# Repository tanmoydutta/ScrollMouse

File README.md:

# Scroll Mouse using manetic angle sensor
A BLE mouse dial for smooth and minimum effort scrolling. 

Powered by nRF52840 BLE Soc, this HID input device is to reduce effort in scrolling. 

## Demo

_Click the image to watch the video._

Here is an open view of the device - 

Here is a complete 3D view of the device - 

The PCB is designed around AS5600 mangetic engle encoder- 

In the center is a 608 2RS Bearing for long boards making the swivel action smooth and long running -

The radial magnet in the center of the bearing floats on top of the AS5600 sensor chip to detect the angle of rotation -

The diametrically magnetised permanent magnet sits in the center of the dial assembly - 

This project is certified as Open Source Hardware - 
<p align="center">
  
</p>

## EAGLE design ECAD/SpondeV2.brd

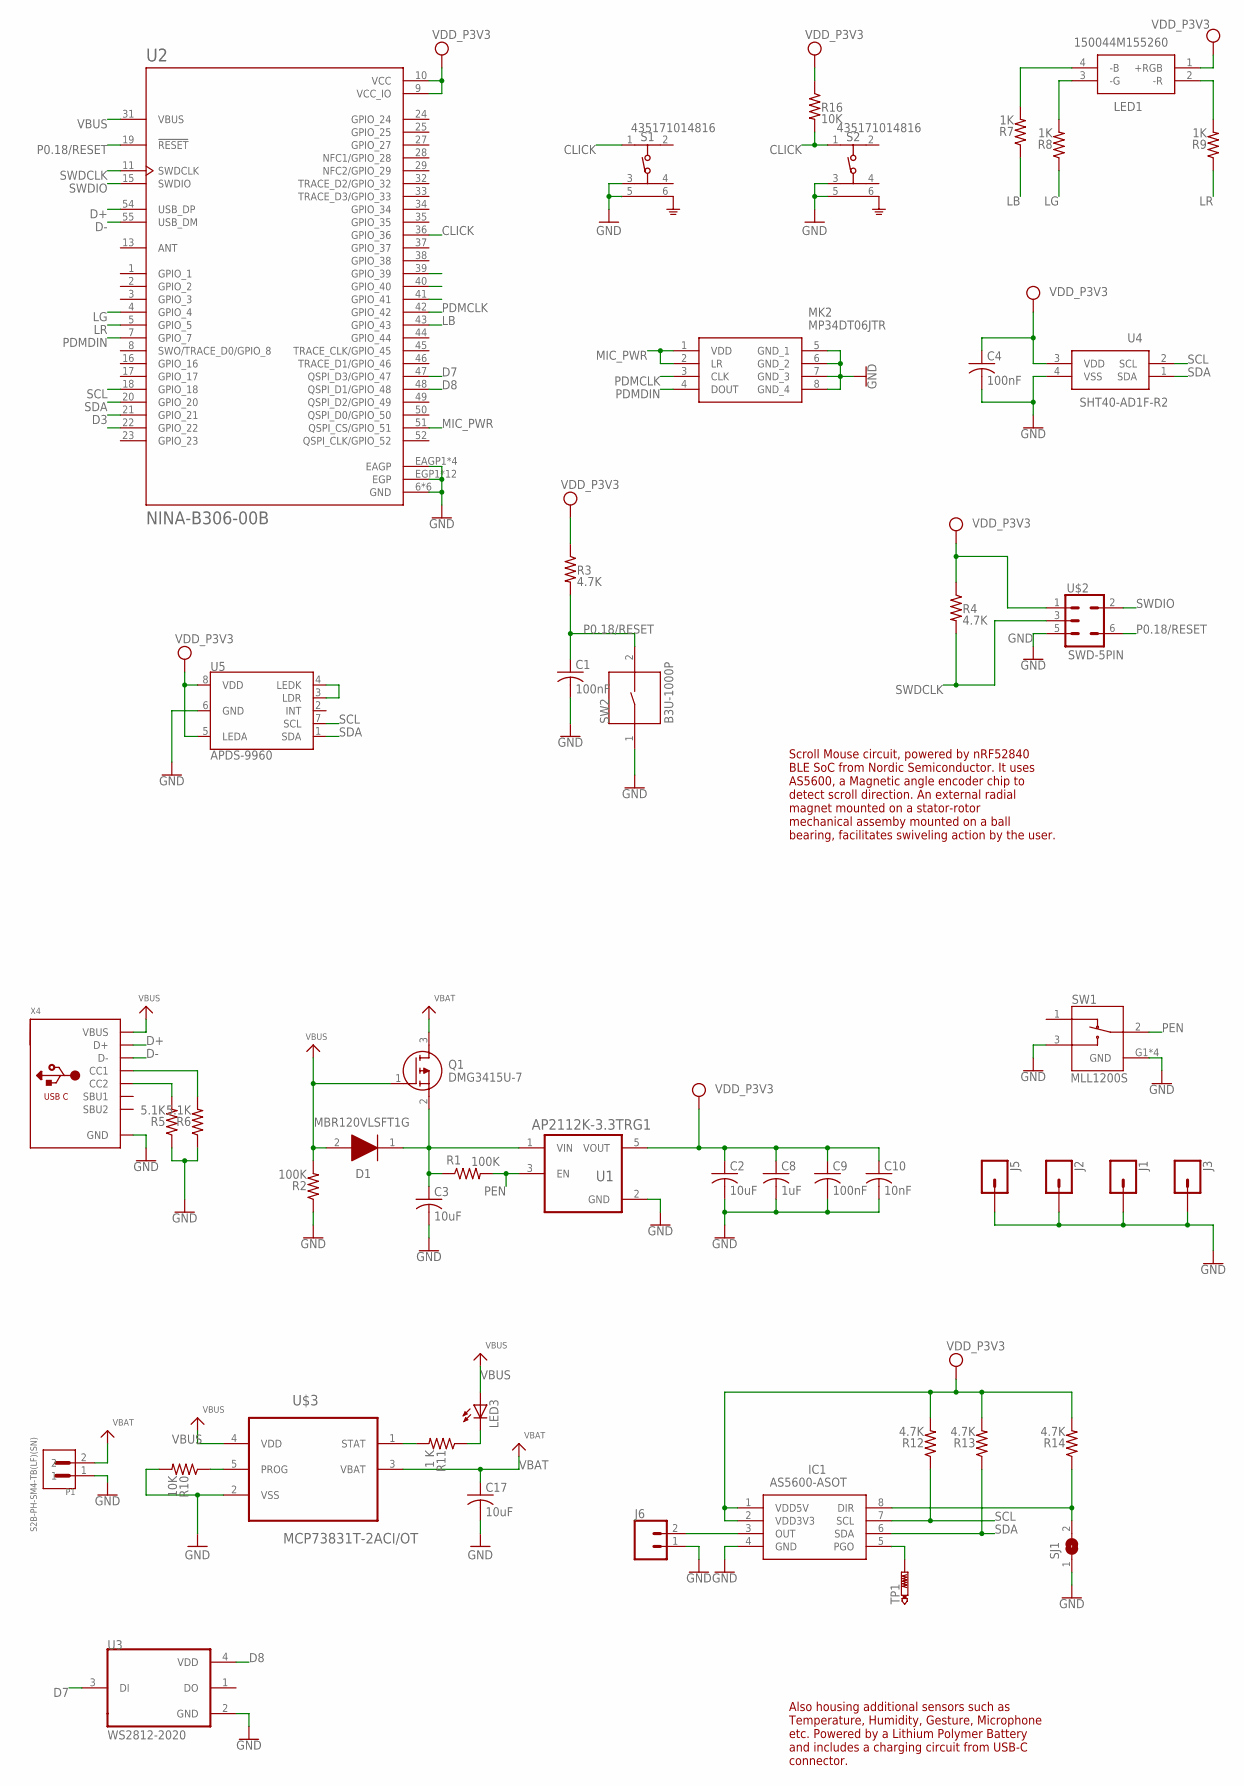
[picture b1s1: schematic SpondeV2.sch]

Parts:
C1, C4, C9: 100nF; C0402
C2, C3, C17: 10uF; C0402
C8: 1uF; C0402
C10: 10nF; C0402
D1: MBR120VLSFT1G; SODFL3616X98N
IC1: AS5600-ASOT; SOIC127P600X175-8N
J1, J2, J3, J5: CONN_01PTH_2MM; 1X01_2MM
J6: CONN_02LOCK_LONGPADS; 1X02_LOCK_LONGPADS
LED1: 150044M155260
LED3: LEDCHIPLED_0603; CHIPLED_0603
MK2: MP34DT06JTR
P1: S2B-PH-SM4-TB(LF)(SN); JST_S2B-PH-SM4-TB(LF)(SN)
Q1: DMG3415U-7; SOT96P240X100-3N
R1, R2: 100K; R0402
R3, R4, R12, R13, R14: 4.7K; R0402
R5, R6: 5.1K; R0402
R7, R8, R9: 1K; R0402
R10, R16: 10K; R0402
R11: 1 K; R0402
S1, S2: 435171014816
SJ1: SJ
SW1: MLL1200S; SW_MLL1200S
SW2: B3U-1000P; SW_B3U-1000P
TP1: PTR1B2,54; B2,54
U1: AP2112K-3.3TRG1; SOT95P285X140-5N
U2: NINA-B306-00B; XCVR_NINA-B306-00B
U3: WS2812-2020; LED_WS2812-2020
U4: SHT40-AD1F-R2; SHT40AD1FR2
U5: APDS-9960
U$2: SWD-5PIN; PAD_05_03X2_TP_NO4
U$3: MCP73831T-2ACI/OT; SOT95P280X145-5N
X4: MICROBUILDER_USB_C; MICROBUILDER_USB_C_CUSB31-CFM2AX-01-X

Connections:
CLICK: R16.2, S1.1, S2.1, U2.36 (GPIO_36)
D3: U2.21 (GPIO_21)
D7: U2.47 (QSPI_D3/GPIO_47), U3.3 (DI)
D8: U2.48 (QSPI_D1/GPIO_48), U3.4 (VDD)
D+: U2.54 (USB_DP), X4.A6 (D+), X4.B6 (D+)
D-: U2.55 (USB_DM), X4.A7 (D-), X4.B7 (D-)
GND: C1.2, C2.2, C3.2, C4.2, C8.2, C9.2, C10.2, C17.2, IC1.4 (GND), J1.1, J2.1, J3.1, J5.1, J6.1, MK2.5 (GND_1), MK2.6 (GND_2), MK2.7 (GND_3), MK2.8 (GND_4), P1.1, R2.1, R5.1, R6.1, R10.2, S1.3, S1.5, S2.3, S2.5, SJ1.1, SW1.3, SW1.G1 (GND), SW1.G2 (GND), SW1.G3 (GND), SW1.G4 (GND), SW2.1, U1.2 (GND), U2.6 (GND), U2.12 (GND), U2.14 (GND), U2.26 (GND), U2.30 (GND), U2.53 (GND), U2.EAGP1 (EAGP), U2.EAGP2 (EAGP), U2.EAGP3 (EAGP), U2.EAGP4 (EAGP), U2.EGP1 (EGP), U2.EGP2 (EGP), U2.EGP3 (EGP), U2.EGP4 (EGP), U2.EGP5 (EGP), U2.EGP6 (EGP), U2.EGP7 (EGP), U2.EGP8 (EGP), U2.EGP9 (EGP), U2.EGP10 (EGP), U2.EGP11 (EGP), U2.EGP12 (EGP), U3.2 (GND), U4.4 (VSS), U5.6 (GND), U$2.5, U$3.2 (VSS), X4.A1B12 (GND), X4.B1A12 (GND)
LB: R7.1, U2.43 (GPIO_43)
LG: R8.1, U2.4 (GPIO_4)
LR: R9.1, U2.5 (GPIO_5)
MIC_PWR: MK2.1 (VDD), MK2.2 (LR), U2.51 (QSPI_CS/GPIO_51)
unnamed: IC1.5 (PGO), TP1.TP
unnamed: R11.2, U$3.1 (STAT)
unnamed: R5.2, X4.B5 (CC2)
unnamed: R6.2, X4.A5 (CC1)
unnamed: C3.1, D1.1 (K), Q1.2 (S), R1.1, U1.1 (VIN)
unnamed: U5.3 (LDR), U5.4 (LEDK)
unnamed: IC1.8 (DIR), R14.1, SJ1.2
unnamed: IC1.3 (OUT), J6.2
unnamed: LED1.4 (-B), R7.2
unnamed: LED1.3 (-G), R8.2
unnamed: R10.1, U$3.5 (PROG)
unnamed: LED3.C, R11.1
unnamed: LED1.2 (-R), R9.2
P0.18/RESET: C1.1, R3.2, SW2.2, U2.19 (!RESET), U$2.6
PDMCLK: MK2.3 (CLK), U2.42 (GPIO_42)
PDMDIN: MK2.4 (DOUT), U2.7 (GPIO_7)
PEN: R1.2, SW1.2, U1.3 (EN)
SCL: IC1.7 (SCL), R12.1, U2.18 (GPIO_18), U4.2 (SCL), U5.7 (SCL)
SDA: IC1.6 (SDA), R13.1, U2.20 (GPIO_20), U4.1 (SDA), U5.1 (SDA)
SWDCLK: R4.2, U2.11 (SWDCLK), U$2.3
SWDIO: U2.15 (SWDIO), U$2.2
VBAT: C17.1, P1.2, Q1.3 (D), U$3.3 (VBAT)
VBUS: D1.2 (A), LED3.A, Q1.1 (G), R2.2, U2.31 (VBUS), U$3.4 (VDD), X4.A4B9 (VBUS), X4.B4A9 (VBUS)
VCC: C2.1, C4.1, C8.1, C9.1, C10.1, IC1.1 (VDD5V), IC1.2 (VDD3V3), LED1.1 (+RGB), R3.1, R4.1, R12.2, R13.2, R14.2, R16.1, U1.5 (VOUT), U2.9 (VCC_IO), U2.10 (VCC), U4.3 (VDD), U5.5 (LEDA), U5.8 (VDD), U$2.1

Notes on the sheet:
Scroll Mouse circuit, powered by nRF52840 BLE SoC from Nordic Semiconductor. It uses AS5600, a Magnetic angle encoder chip to detect scroll direction. An external radial magnet mounted on a stator-rotor mechanical assemby mounted on a ball bearing, facilitates swiveling action by the user.
Also housing additional sensors such as Temperature, Humidity, Gesture, Microphone etc. Powered by a Lithium Polymer Battery and includes a charging circuit from USB-C connector.

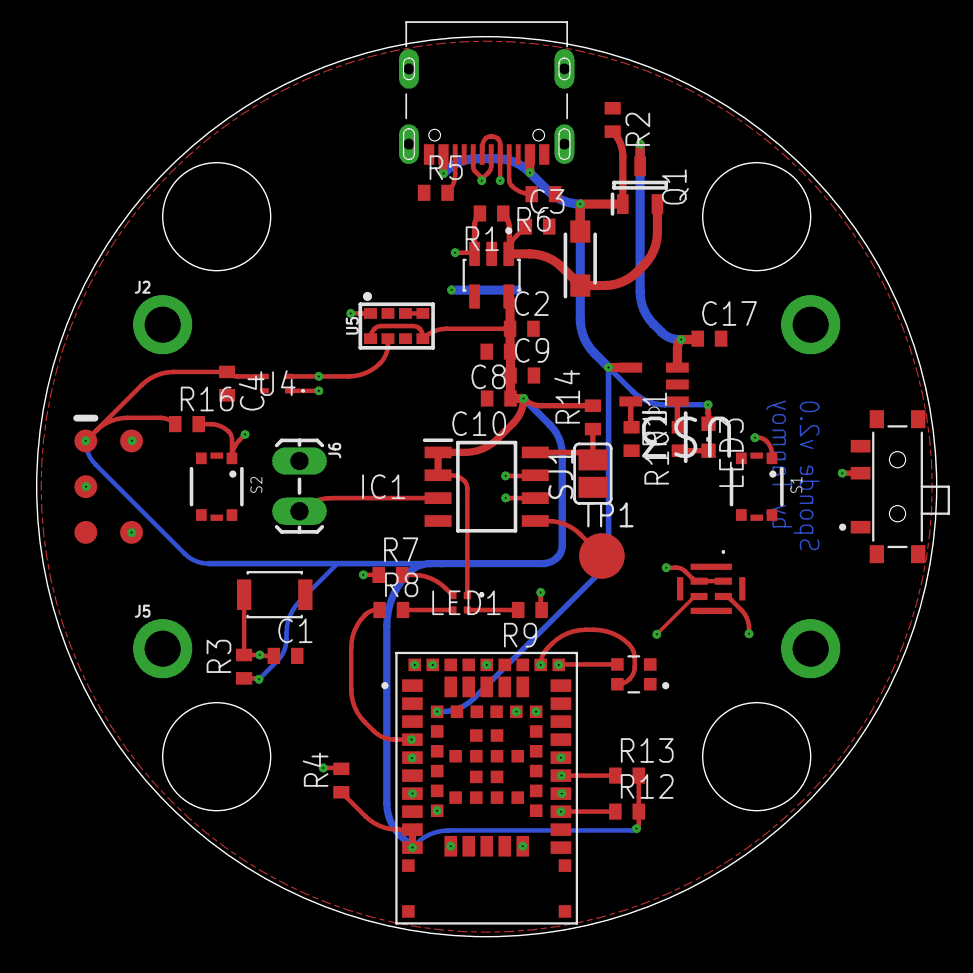
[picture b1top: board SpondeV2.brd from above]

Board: 6 copper layers, 50.0 x 50.0 mm, 49 parts (1 on the bottom side), 34 nets.

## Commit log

2026-06-08 Adding documentaion
2026-06-09 Update project name in README
2026-06-12 Adding OSHWA mark
2026-06-29 Remove tracked .DS_Store file
2026-06-29 Add demo video to README
2026-06-29 Replace demo video with smaller file

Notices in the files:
parts and their libraries:
SparkFun-Connectors: Licensing: Creative Commons ShareAlike 4.0 International - https://creativecommons.org/licenses/by-sa/4.0
